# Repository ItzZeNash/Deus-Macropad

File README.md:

Finished! 
https://www.reddit.com/user/Revanence01/comments/1q9oqgf/deusmacropad/

# Deus-Macropad
A Macropad for personal use in Blender, Davinci and daily life. 4 keys

Schematic

PCB Layout

Case Design
BOTTOM

 TOP

Assembly- Assemble the pcb and XIAO, and insert into the bottom case then put on the top case screw and add the heated insert to hold the screws. Either order both side assembly or solder on the keys and the microcontroller.
Where there are holes add screws 
 including pcb (no worries due to alr having mounting holes in pcb)

| Part | Quantity | Notes |
|------|----------|--------|
| Seeed XIAO RP2040 (through‑hole) | 1 |
| MX‑style switches | 4 |
| M3 heat‑set inserts | 4 | For case mounting |
| M3x16mm screws | 8 | For assembly |
| 3D printed case | 1 set |
| PCB | 1 |
Case preferably in a frosted white/frosted transparent colorway.
Also keycaps 4, preferably pbt.

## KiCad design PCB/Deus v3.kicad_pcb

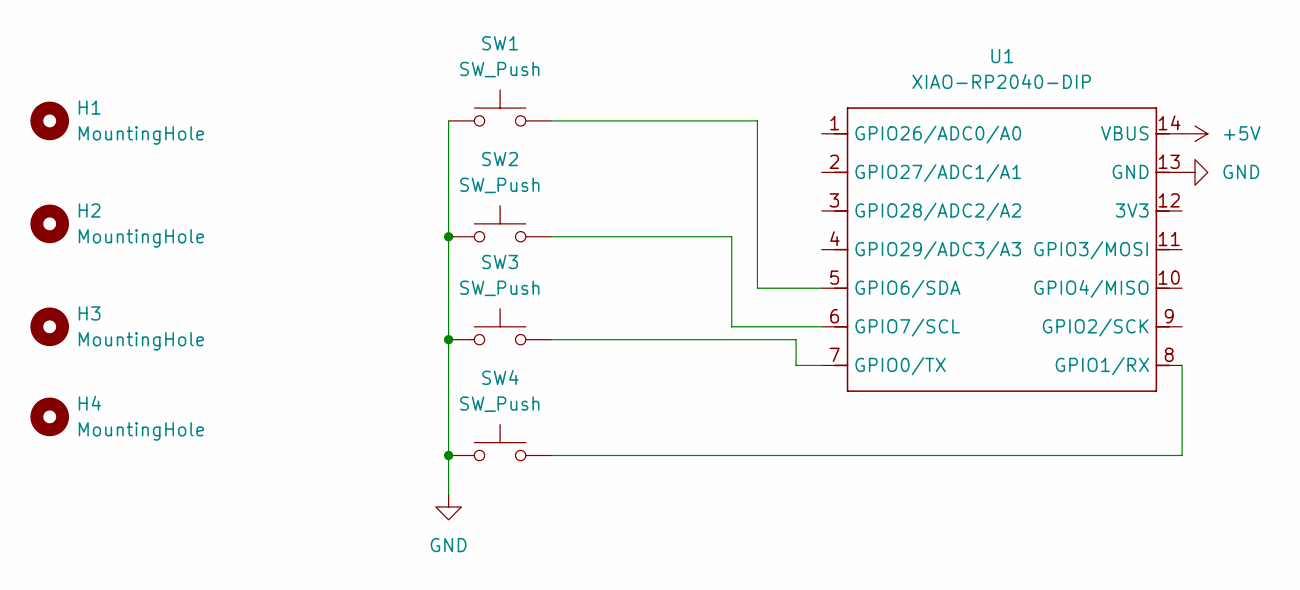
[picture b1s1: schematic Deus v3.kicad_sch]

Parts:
H1, H2, H3, H4: MountingHole; MountingHole_3.2mm_M3_Pad
SW1, SW2, SW3, SW4: SW_Push; SW_Cherry_MX_1.00u_PCB
U1: XIAO-RP2040-DIP

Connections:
+5V: U1.14 (VBUS)
GND: SW1.1, SW2.1, SW3.1, SW4.1, U1.13 (GND)
unnamed: SW3.2, U1.7 (GPIO0/TX)
unnamed: SW4.2, U1.8 (GPIO1/RX)
unnamed: SW1.2, U1.5 (GPIO6/SDA)
unnamed: SW2.2, U1.6 (GPIO7/SCL)

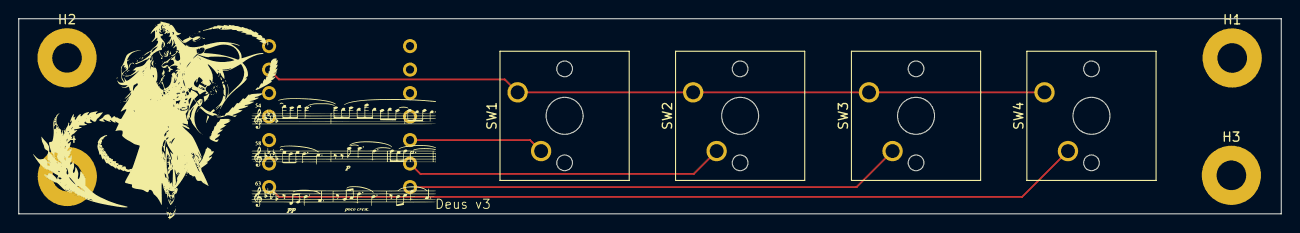
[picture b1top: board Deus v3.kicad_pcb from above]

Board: 2 copper layers, 136.5 x 21.1 mm, 9 parts (1 on the bottom side), 5 nets.

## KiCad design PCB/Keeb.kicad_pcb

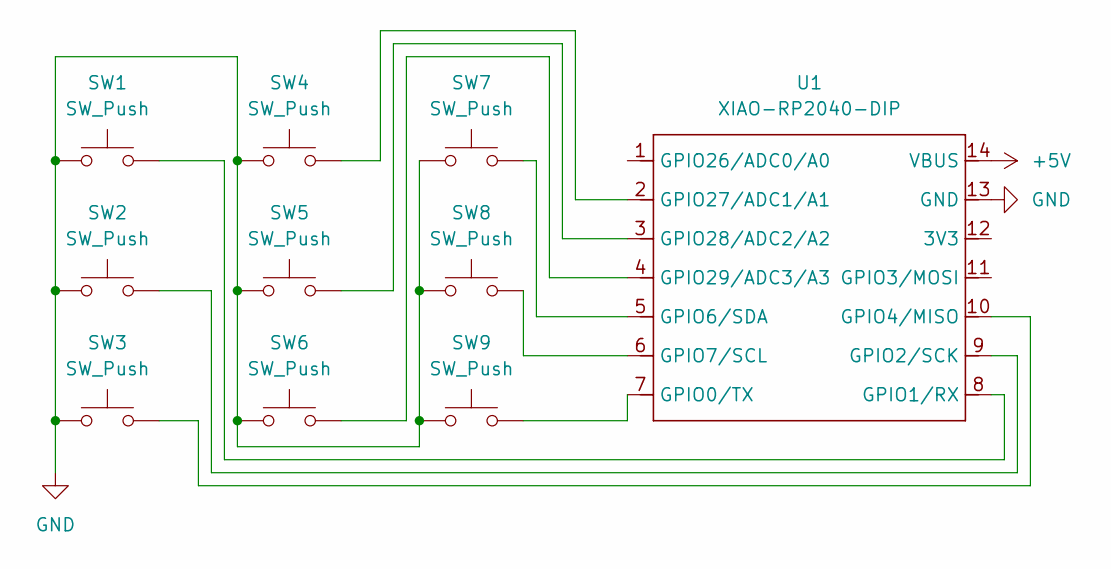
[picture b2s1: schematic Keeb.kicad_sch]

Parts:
SW1, SW2, SW3, SW4, SW5, SW6, SW7, SW8, SW9: SW_Push; SW_Cherry_MX_1.00u_PCB
U1: XIAO-RP2040-DIP

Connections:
+5V: U1.14 (VBUS)
GND: SW1.1, SW2.1, SW3.1, SW4.1, SW5.1, SW6.1, SW7.1, SW8.1, SW9.1, U1.13 (GND)
unnamed: SW9.2, U1.7 (GPIO0/TX)
unnamed: SW1.2, U1.8 (GPIO1/RX)
unnamed: SW2.2, U1.9 (GPIO2/SCK)
unnamed: SW3.2, U1.10 (GPIO4/MISO)
unnamed: SW7.2, U1.5 (GPIO6/SDA)
unnamed: SW8.2, U1.6 (GPIO7/SCL)
unnamed: SW4.2, U1.2 (GPIO27/ADC1/A1)
unnamed: SW5.2, U1.3 (GPIO28/ADC2/A2)
unnamed: SW6.2, U1.4 (GPIO29/ADC3/A3)

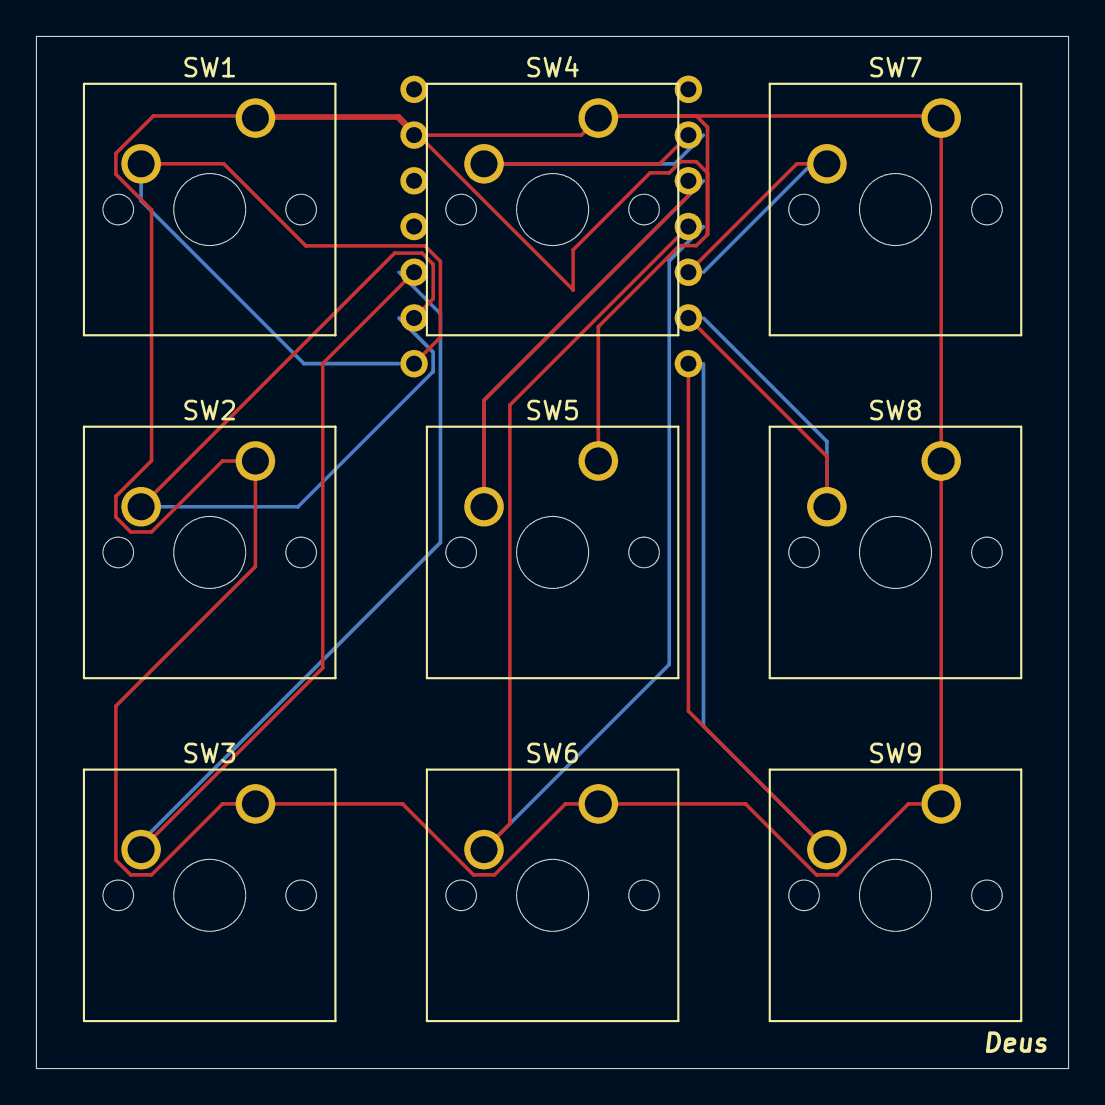
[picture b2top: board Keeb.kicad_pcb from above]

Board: 2 copper layers, 57.3 x 57.3 mm, 10 parts (1 on the bottom side), 10 nets.

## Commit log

2025-12-22 Create CAD
2025-12-22 Add new temporary file in CAD directory
2025-12-22 Add new temporary file in PCB directory
2025-12-22 Add new temp file to Firmware directory
2025-12-22 Initialize KMK keyboard firmware with keymap
2025-12-22 Add USB storage and CDC initialization in boot.py
2025-12-22 Add temp directory in Firmware/KMK
2025-12-22 Add temp directory to Firmware/KMK
2025-12-22 Enhance README with schematic and case design details
    Added detailed sections for schematic, PCB layout, case design, and parts list.
2025-12-23 Revise README for Macropad design updates
    Updated the README to reflect changes in the Macropad design and assembly instructions.
2025-12-23 Add new temp file in graphics.pretty directory
2025-12-23 Refactor pin assignments and keymap configuration
2025-12-23 Update README to include daily life usage
2025-12-23 Update assembly instructions in README
    Added additional instructions for assembly process.
2025-12-23 Correct screw quantity in assembly instructions
    Updated the quantity of M3x16mm screws from 4 to 8 in the assembly instructions.
2025-12-23 Include keycaps specification in README
    Added keycaps requirement to the README.
2026-01-11 Refactor keyboard configuration and keymap
2026-01-11 Update README with project status and link
    Added a note about the project being finished and a link to Reddit.
2026-01-16 Update README with image and text changes
    Added an image to the README and updated text.
